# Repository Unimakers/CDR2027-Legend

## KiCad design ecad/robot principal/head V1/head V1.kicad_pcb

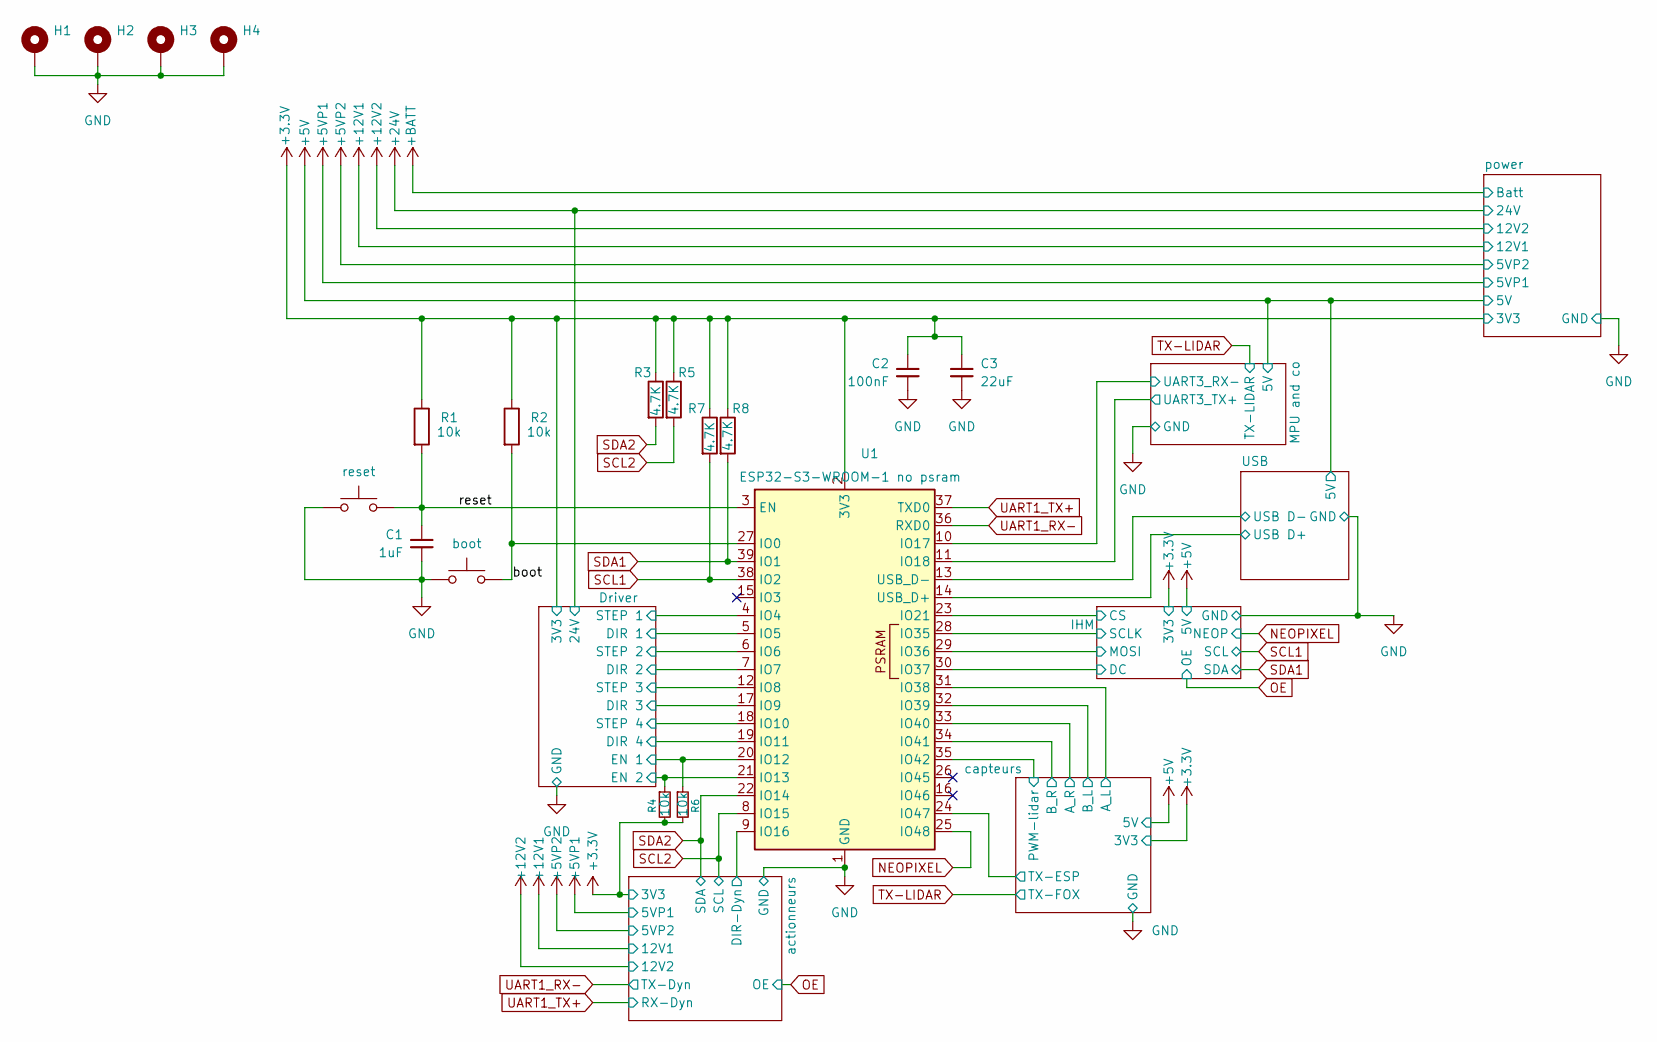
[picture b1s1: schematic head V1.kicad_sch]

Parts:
C1: 1uF; C_0805_2012Metric_Pad1.18x1.45mm_HandSolder
C2: 100nF; C_0805_2012Metric_Pad1.18x1.45mm_HandSolder
C3: 22uF; C_0805_2012Metric_Pad1.18x1.45mm_HandSolder
H1, H2, H3, H4: MountingHole_Pad; MountingHole_3.2mm_M3_Pad_Via
R1, R2, R4, R6: 10k; R_0805_2012Metric_Pad1.20x1.40mm_HandSolder
R3, R5, R7, R8: 4.7K; R_0805_2012Metric_Pad1.20x1.40mm_HandSolder
SW1: reset; SW_Push_SPST_NO_Alps_SKRK
SW2: boot; SW_Push_SPST_NO_Alps_SKRK
U1: ESP32-S3-WROOM-1 no psram; ESP32-S3-WROOM-1

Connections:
+3.3V: C2.1, C3.1, R1.1, R2.1, R3.1, R4.2, R5.1, R6.2, R7.1, R8.1, U1.2 (3V3); also elsewhere on the board
/Driver/DIR 1: U1.5 (IO5); also elsewhere on the board
/Driver/DIR 2: U1.7 (IO7); also elsewhere on the board
/Driver/DIR 3: U1.17 (IO9); also elsewhere on the board
/Driver/DIR 4: U1.19 (IO11); also elsewhere on the board
/Driver/EN 1: R6.1, U1.20 (IO12); also elsewhere on the board
/Driver/EN 2: R4.1, U1.21 (IO13); also elsewhere on the board
/Driver/STEP 1: U1.4 (IO4); also elsewhere on the board
/Driver/STEP 2: U1.6 (IO6); also elsewhere on the board
/Driver/STEP 3: U1.12 (IO8); also elsewhere on the board
/Driver/STEP 4: U1.18 (IO10); also elsewhere on the board
/IHM/CS: U1.23 (IO21); also elsewhere on the board
/IHM/DC: U1.30 (IO37); also elsewhere on the board
/IHM/MOSI: U1.29 (IO36); also elsewhere on the board
/IHM/SCLK: U1.28 (IO35); also elsewhere on the board
/MPU and co/UART3_RX-: U1.10 (IO17); also elsewhere on the board
/MPU and co/UART3_TX+: U1.11 (IO18); also elsewhere on the board
/USB/USB D+: U1.14 (USB_D+); also elsewhere on the board
/USB/USB D-: U1.13 (USB_D-); also elsewhere on the board
/actionneurs/DIR-Dyn: U1.9 (IO16); also elsewhere on the board
/boot: R2.2, SW2.2, U1.27 (IO0)
/capteurs/A_L: U1.31 (IO38); also elsewhere on the board
/capteurs/A_R: U1.33 (IO40); also elsewhere on the board
/capteurs/B_L: U1.32 (IO39); also elsewhere on the board
/capteurs/B_R: U1.34 (IO41); also elsewhere on the board
/capteurs/PWM-lidar: U1.35 (IO42); also elsewhere on the board
/capteurs/TX-ESP: U1.24 (IO47); also elsewhere on the board
/reset: C1.1, R1.2, SW1.2, U1.3 (EN)
GND: C1.2, C2.2, C3.2, H1.1 (1_1), H2.1 (1_1), H3.1 (1_1), H4.1 (1_1), SW1.1, SW2.1, U1.1 (GND), U1.40 (GND), U1.41 (GND); also elsewhere on the board
NEOPIXEL: U1.25 (IO48); also elsewhere on the board
SCL1: R7.2, U1.38 (IO2); also elsewhere on the board
SCL2: R5.2, U1.8 (IO15); also elsewhere on the board
SDA1: R8.2, U1.39 (IO1); also elsewhere on the board
SDA2: R3.2, U1.22 (IO14); also elsewhere on the board
UART1_RX-: U1.36 (RXD0); also elsewhere on the board
UART1_TX+: U1.37 (TXD0); also elsewhere on the board

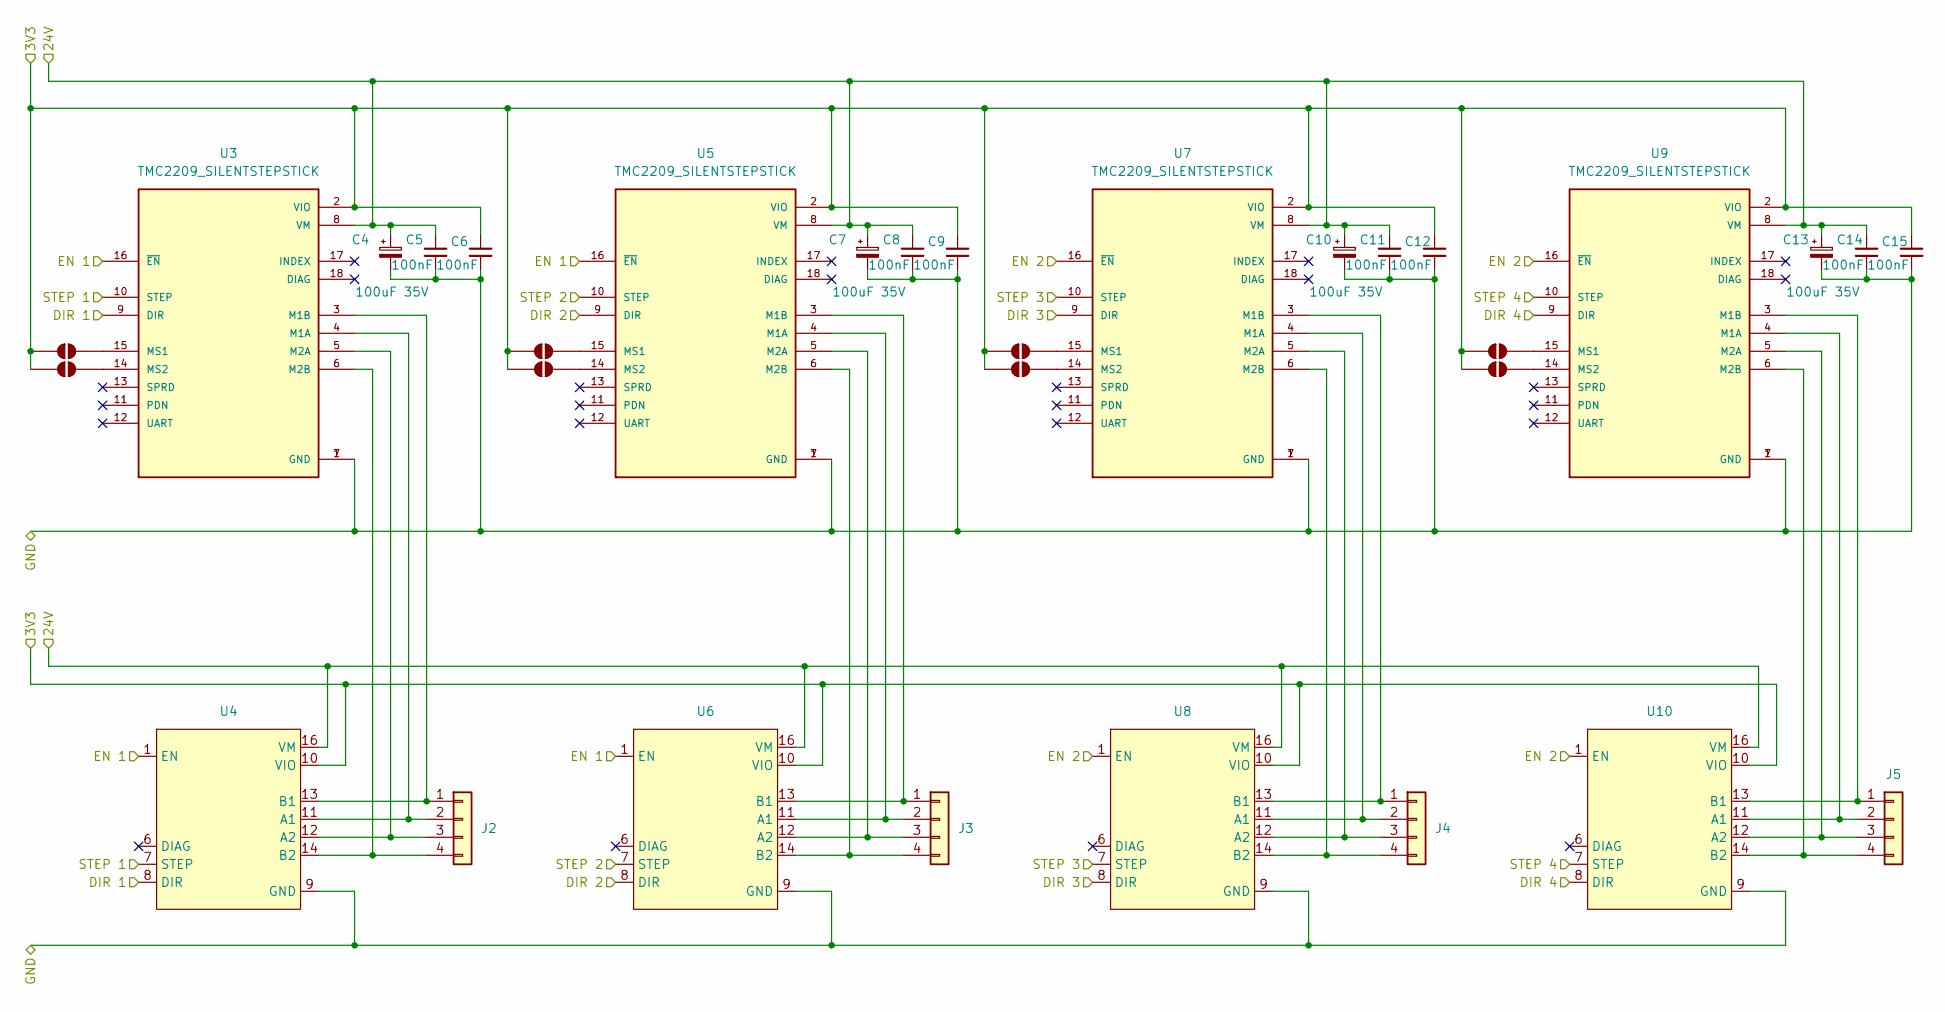
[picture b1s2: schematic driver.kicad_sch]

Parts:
C4, C7, C10, C13: 100uF 35V; CP_Radial_D6.3mm_P2.50mm
C5, C6, C8, C9, C11, C12, C14, C15: 100nF; C_0805_2012Metric_Pad1.18x1.45mm_HandSolder
J2, J3, J4, J5: Conn_01x04; Molex_KK-254_AE-6410-04A_1x04_P2.54mm_Vertical
JP1, JP2, JP3, JP4, JP5, JP6, JP7, JP8: SolderJumper_2_Open; SolderJumper-2_P1.3mm_Open_RoundedPad1.0x1.5mm
U3, U5, U7, U9: TMC2209_SILENTSTEPSTICK; MODULE_TMC2209_SILENTSTEPSTICK; PARTREV 1.20
U4, U6, U8, U10: ez 2209

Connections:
+3.3V: C6.1, C9.1, C12.1, C15.1, JP1.1 (A), JP2.1 (A), JP3.1 (A), JP4.1 (A), JP5.1 (A), JP6.1 (A), JP7.1 (A), JP8.1 (A), U3.2 (VIO), U4.10 (VIO), U5.2 (VIO), U6.10 (VIO), U7.2 (VIO), U8.10 (VIO), U9.2 (VIO), U10.10 (VIO); also elsewhere on the board
+24V: C4.1, C5.1, C7.1, C8.1, C10.1, C11.1, C13.1, C14.1, U3.8 (VM), U4.16 (VM), U5.8 (VM), U6.16 (VM), U7.8 (VM), U8.16 (VM), U9.8 (VM), U10.16 (VM); also elsewhere on the board
/Driver/DIR 1: U3.9 (DIR), U4.8 (DIR); also elsewhere on the board
/Driver/DIR 2: U5.9 (DIR), U6.8 (DIR); also elsewhere on the board
/Driver/DIR 3: U7.9 (DIR), U8.8 (DIR); also elsewhere on the board
/Driver/DIR 4: U9.9 (DIR), U10.8 (DIR); also elsewhere on the board
/Driver/EN 1: U3.16 (~EN), U4.1 (EN), U5.16 (~EN), U6.1 (EN); also elsewhere on the board
/Driver/EN 2: U7.16 (~EN), U8.1 (EN), U9.16 (~EN), U10.1 (EN); also elsewhere on the board
/Driver/STEP 1: U3.10 (STEP), U4.7 (STEP); also elsewhere on the board
/Driver/STEP 2: U5.10 (STEP), U6.7 (STEP); also elsewhere on the board
/Driver/STEP 3: U7.10 (STEP), U8.7 (STEP); also elsewhere on the board
/Driver/STEP 4: U9.10 (STEP), U10.7 (STEP); also elsewhere on the board
GND: C4.2, C5.2, C6.2, C7.2, C8.2, C9.2, C10.2, C11.2, C12.2, C13.2, C14.2, C15.2, U3.1 (GND), U3.7 (GND), U4.9 (GND), U4.15 (GND), U5.1 (GND), U5.7 (GND), U6.9 (GND), U6.15 (GND), U7.1 (GND), U7.7 (GND), U8.9 (GND), U8.15 (GND), U9.1 (GND), U9.7 (GND), U10.9 (GND), U10.15 (GND); also elsewhere on the board
unnamed: J2.1, U3.3 (M1B), U4.13 (B1)
unnamed: J2.2, U3.4 (M1A), U4.11 (A1)
unnamed: J2.3, U3.5 (M2A), U4.12 (A2)
unnamed: J2.4, U3.6 (M2B), U4.14 (B2)
unnamed: J3.1, U5.3 (M1B), U6.13 (B1)
unnamed: J3.2, U5.4 (M1A), U6.11 (A1)
unnamed: J3.3, U5.5 (M2A), U6.12 (A2)
unnamed: J3.4, U5.6 (M2B), U6.14 (B2)
unnamed: J4.1, U7.3 (M1B), U8.13 (B1)
unnamed: J4.2, U7.4 (M1A), U8.11 (A1)
unnamed: J4.3, U7.5 (M2A), U8.12 (A2)
unnamed: J4.4, U7.6 (M2B), U8.14 (B2)
unnamed: J5.1, U9.3 (M1B), U10.13 (B1)
unnamed: J5.2, U9.4 (M1A), U10.11 (A1)
unnamed: J5.3, U9.5 (M2A), U10.12 (A2)
unnamed: J5.4, U9.6 (M2B), U10.14 (B2)
unnamed: JP1.2 (B), U3.15 (MS1)
unnamed: JP2.2 (B), U3.14 (MS2)
unnamed: JP3.2 (B), U5.15 (MS1)
unnamed: JP4.2 (B), U5.14 (MS2)
unnamed: JP5.2 (B), U7.15 (MS1)
unnamed: JP6.2 (B), U7.14 (MS2)
unnamed: JP7.2 (B), U9.15 (MS1)
unnamed: JP8.2 (B), U9.14 (MS2)

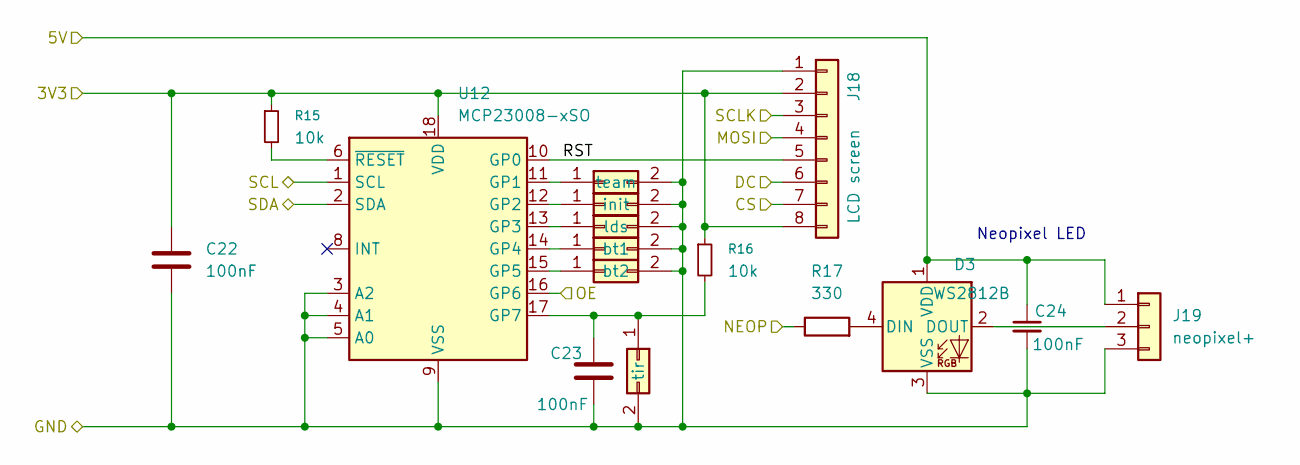
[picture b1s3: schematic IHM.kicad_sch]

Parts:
C22, C23, C24: 100nF; C_0805_2012Metric_Pad1.18x1.45mm_HandSolder
D3: WS2812B; LED_WS2812B_PLCC4_5.0x5.0mm_P3.2mm
J12: team; Molex_KK-254_AE-6410-02A_1x02_P2.54mm_Vertical
J13: init; Molex_KK-254_AE-6410-02A_1x02_P2.54mm_Vertical
J14: lds; Molex_KK-254_AE-6410-02A_1x02_P2.54mm_Vertical
J15: bt1; Molex_KK-254_AE-6410-02A_1x02_P2.54mm_Vertical
J16: bt2; Molex_KK-254_AE-6410-02A_1x02_P2.54mm_Vertical
J17: tir; Molex_KK-254_AE-6410-02A_1x02_P2.54mm_Vertical
J18: LCD screen; PinSocket_1x08_P2.54mm_Vertical
J19: neopixel+; Molex_KK-254_AE-6410-03A_1x03_P2.54mm_Vertical
R15, R16: 10k; R_0805_2012Metric_Pad1.20x1.40mm_HandSolder
R17: 330; R_0805_2012Metric_Pad1.20x1.40mm_HandSolder
U12: MCP23008-xSO; SOIC-18W_7.5x11.6mm_P1.27mm

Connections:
+3.3V: C22.1, J18.2, J18.8, R15.1, R16.1, U12.18 (VDD); also elsewhere on the board
+5V: C24.1, D3.1 (VDD), J19.1; also elsewhere on the board
/IHM/CS: J18.7; also elsewhere on the board
/IHM/DC: J18.6; also elsewhere on the board
/IHM/MOSI: J18.4; also elsewhere on the board
/IHM/RST: J18.5, U12.10 (GP0)
/IHM/SCLK: J18.3; also elsewhere on the board
GND: C22.2, C23.2, C24.2, D3.3 (VSS), J12.2, J13.2, J14.2, J15.2, J16.2, J17.2, J18.1, J19.3, U12.3 (A2), U12.4 (A1), U12.5 (A0), U12.9 (VSS); also elsewhere on the board
NEOPIXEL: R17.1; also elsewhere on the board
unnamed: D3.4 (DIN), R17.2
unnamed: D3.2 (DOUT), J19.2
unnamed: J12.1, U12.11 (GP1)
unnamed: J13.1, U12.12 (GP2)
unnamed: J14.1, U12.13 (GP3)
unnamed: J15.1, U12.14 (GP4)
unnamed: J16.1, U12.15 (GP5)
unnamed: C23.1, J17.1, R16.2, U12.17 (GP7)
unnamed: R15.2, U12.6 (~RESET)
OE: U12.16 (GP6); also elsewhere on the board
SCL1: U12.1 (SCL); also elsewhere on the board
SDA1: U12.2 (SDA); also elsewhere on the board

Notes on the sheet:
Neopixel LED

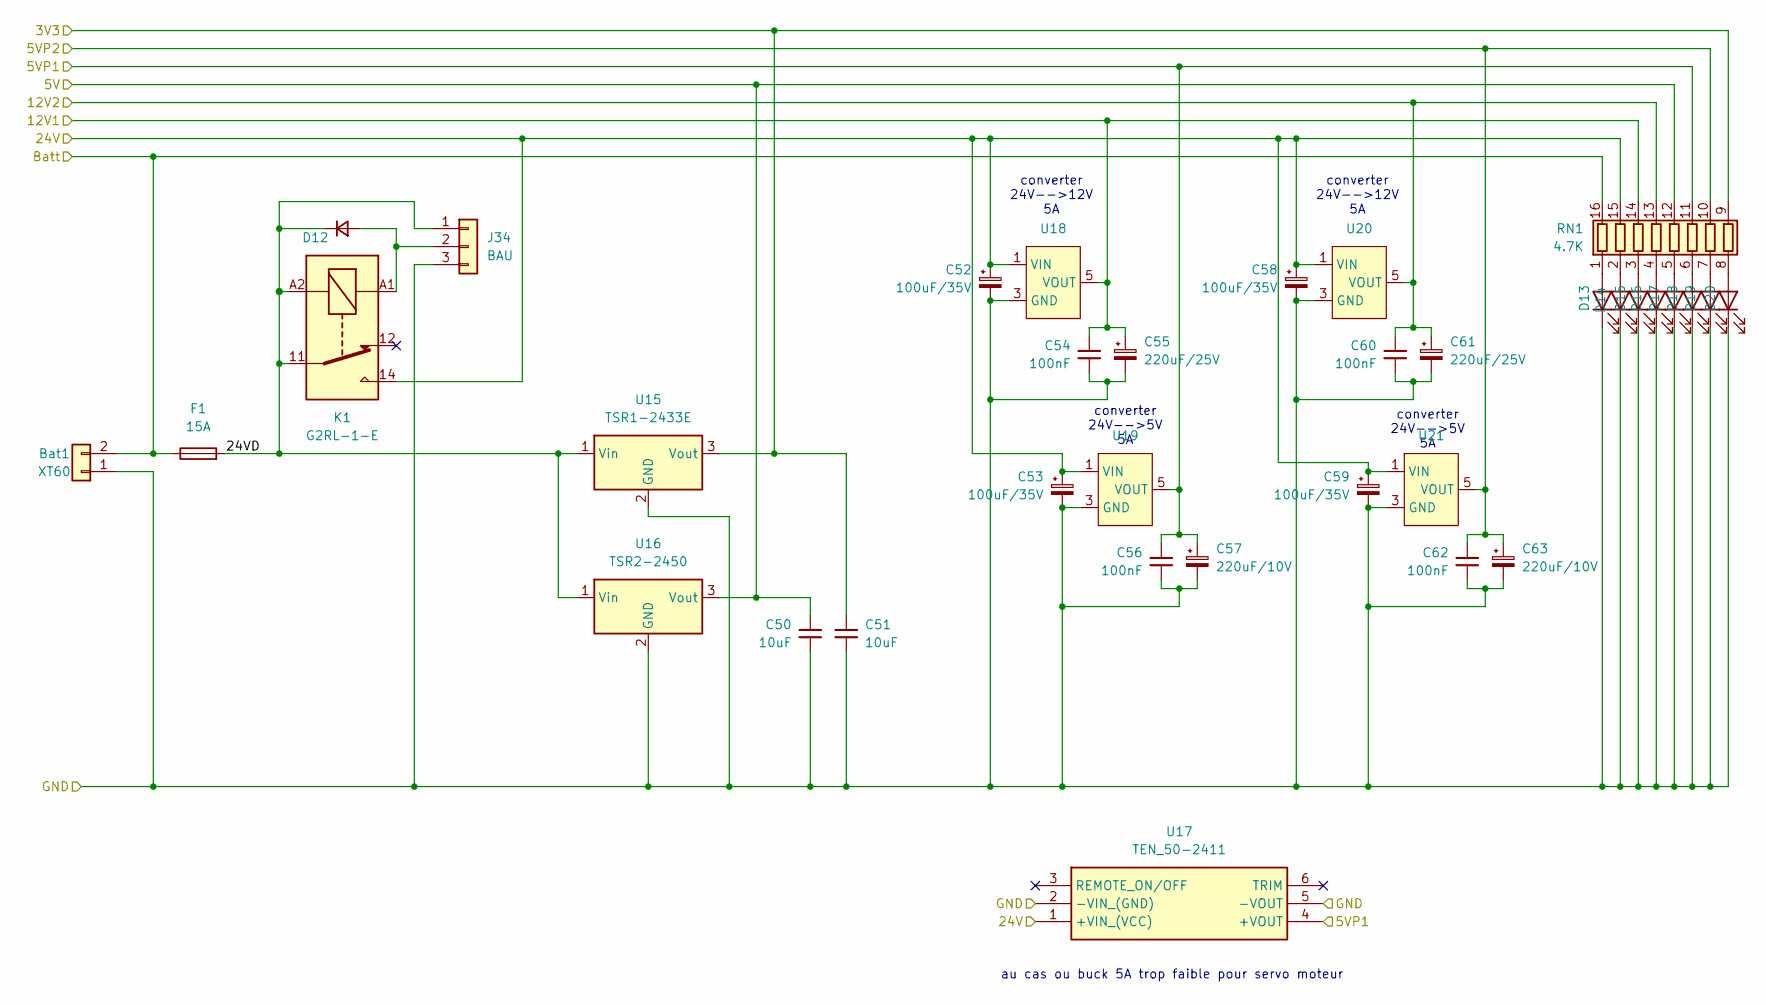
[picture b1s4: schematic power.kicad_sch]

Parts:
Bat1: XT60; AMASS_XT60-M_1x02_P7.20mm_Vertical
C50, C51: 10uF; C_0805_2012Metric_Pad1.18x1.45mm_HandSolder
C52, C53, C58, C59: 100uF/35V; CP_Radial_D6.3mm_P2.50mm
C54, C56, C60, C62: 100nF; C_0805_2012Metric_Pad1.18x1.45mm_HandSolder
C55, C61: 220uF/25V; CP_Radial_D8.0mm_P3.50mm
C57, C63: 220uF/10V; CP_Radial_D6.3mm_P2.50mm
D12: D_Small; D_SMA_Handsoldering
D13, D14, D15, D16, D17, D18, D19, D20: LED; LED_0805_2012Metric_Pad1.15x1.40mm_HandSolder
F1: 15A; Fuseholder_Blade_Mini_Keystone_3568
J34: BAU; Molex_KK-254_AE-6410-03A_1x03_P2.54mm_Vertical
K1: G2RL-1-E; Relay_SPDT_Omron_G2RL-1-E
RN1: 4.7K; R_Array_Convex_8x0602
U15: TSR1-2433E; Converter_DCDC_TRACO_TSR1-xxxxE_THT
U16: TSR2-2450; Converter_DCDC_TRACO_TSR2-xxxx_THT
U17: TEN_50-2411; Mouser Part Number 495-TEN-50-2411
U18, U19, U20, U21: Module_Buck_LMR51450_1x06_P2.54mm

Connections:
+3.3V: C51.1, RN1.9 (R8.2), U15.3 (Vout); also elsewhere on the board
+5V: C50.1, RN1.12 (R5.2), U16.3 (Vout); also elsewhere on the board
+5VP1: C56.1, C57.1, RN1.11 (R6.2), U17.4 (+VOUT), U19.5 (VOUT), U19.6 (VOUT); also elsewhere on the board
+5VP2: C62.1, C63.1, RN1.10 (R7.2), U21.5 (VOUT), U21.6 (VOUT); also elsewhere on the board
+12V1: C54.1, C55.1, RN1.14 (R3.2), U18.5 (VOUT), U18.6 (VOUT); also elsewhere on the board
+12V2: C60.1, C61.1, RN1.13 (R4.2), U20.5 (VOUT), U20.6 (VOUT); also elsewhere on the board
+24V: C52.1, C53.1, C58.1, C59.1, K1.14, RN1.15 (R2.2), U17.1 (+VIN_(VCC)), U18.1 (VIN), U18.2 (VIN), U19.1 (VIN), U19.2 (VIN), U20.1 (VIN), U20.2 (VIN), U21.1 (VIN), U21.2 (VIN); also elsewhere on the board
+BATT: Bat1.2, F1.1, RN1.16 (R1.2)
/power/24VD: D12.1 (K), F1.2, J34.1, K1.11, K1.A2, U15.1 (Vin), U16.1 (Vin)
GND: Bat1.1, C50.2, C51.2, C52.2, C53.2, C54.2, C55.2, C56.2, C57.2, C58.2, C59.2, C60.2, C61.2, C62.2, C63.2, D13.1 (K), D14.1 (K), D15.1 (K), D16.1 (K), D17.1 (K), D18.1 (K), D19.1 (K), D20.1 (K), J34.3, U15.2 (GND), U16.2 (GND), U17.2 (-VIN_(GND)), U17.5 (-VOUT), U18.3 (GND), U18.4 (GND), U19.3 (GND), U19.4 (GND), U20.3 (GND), U20.4 (GND), U21.3 (GND), U21.4 (GND); also elsewhere on the board
unnamed: D12.2 (A), J34.2, K1.A1
unnamed: D13.2 (A), RN1.1 (R1.1)
unnamed: D14.2 (A), RN1.2 (R2.1)
unnamed: D15.2 (A), RN1.3 (R3.1)
unnamed: D16.2 (A), RN1.4 (R4.1)
unnamed: D17.2 (A), RN1.5 (R5.1)
unnamed: D18.2 (A), RN1.6 (R6.1)
unnamed: D19.2 (A), RN1.7 (R7.1)
unnamed: D20.2 (A), RN1.8 (R8.1)

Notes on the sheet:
converter 24V-->12V 5A
converter 24V-->5V 5A
au cas ou buck 5A trop faible pour servo moteur

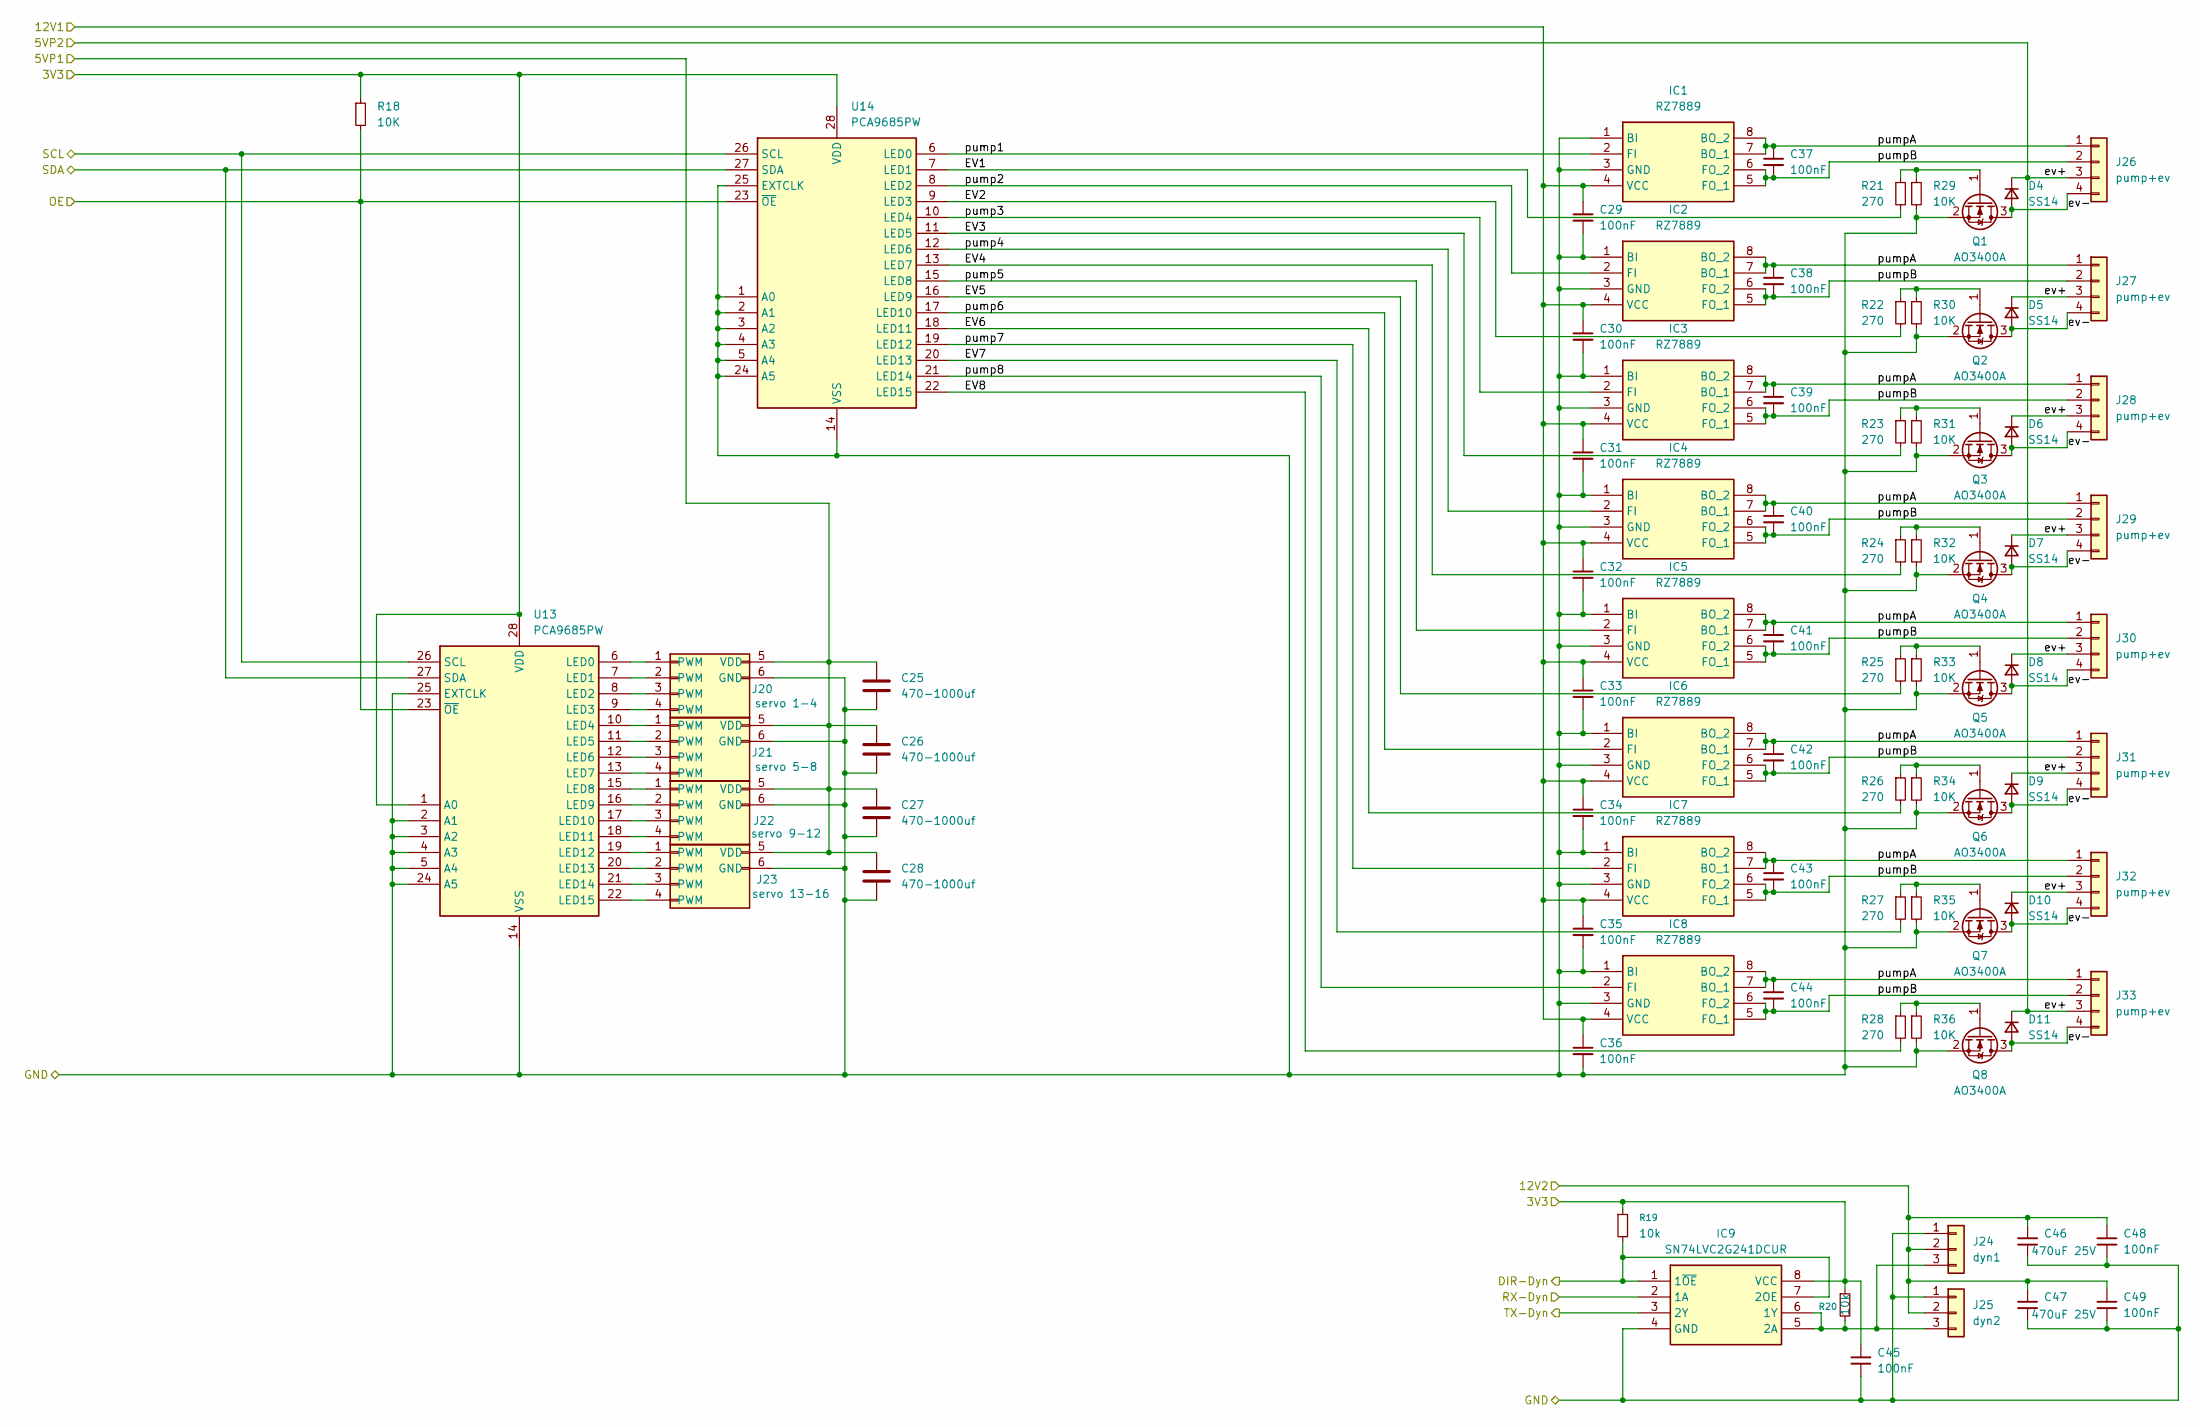
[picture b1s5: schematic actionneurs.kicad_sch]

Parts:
C25, C26, C27, C28: 470-1000uf; CP_Radial_D10.0mm_P5.00mm
C29, C30, C31, C32, C33, C34, C35, C36, C37, C38, C39, C40, C41, C42, C43, C44, C45, C48, C49: 100nF; C_0805_2012Metric_Pad1.18x1.45mm_HandSolder
C46, C47: 470uF 25V; CP_Radial_D10.0mm_P5.00mm
D4, D5, D6, D7, D8, D9, D10, D11: SS14; D_SMA
IC1, IC2, IC3, IC4, IC5, IC6, IC7, IC8: RZ7889; SOIC127P600X175-8N; Manufacturer_Part_Number RZ7889
IC9: SN74LVC2G241DCUR; SOP50P310X90-8N; Mouser Part Number 595-SN74LVC2G241DCUR
J20: servo 1-4; servo
J21: servo 5-8; servo
J22: servo 9-12; servo
J23: servo 13-16; servo
J24: dyn1; Molex_SPOX_5267-03A_1x03_P2.50mm_Vertical
J25: dyn2; Molex_SPOX_5267-03A_1x03_P2.50mm_Vertical
J26, J27, J28, J29, J30, J31, J32, J33: pump+ev; Molex_KK-254_AE-6410-04A_1x04_P2.54mm_Vertical
Q1, Q2, Q3, Q4, Q5, Q6, Q7, Q8: AO3400A; SOT-23
R18, R29, R30, R31, R32, R33, R34, R35, R36: 10K; R_0805_2012Metric_Pad1.20x1.40mm_HandSolder
R19, R20: 10k; R_0805_2012Metric_Pad1.20x1.40mm_HandSolder
R21, R22, R23, R24, R25, R26, R27, R28: 270; R_0805_2012Metric_Pad1.20x1.40mm_HandSolder
U13, U14: PCA9685PW; TSSOP-28_4.4x9.7mm_P0.65mm

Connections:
+3.3V: C45.1, IC9.8 (VCC), R18.1, R19.1, R20.1, U13.1 (A0), U13.28 (VDD), U14.28 (VDD); also elsewhere on the board
+5VP1: C25.1, C26.1, C27.1, C28.1, J20.5 (VDD), J20.7 (VDD), J20.9 (VDD), J20.11 (VDD), J21.5 (VDD), J21.7 (VDD), J21.9 (VDD), J21.11 (VDD), J22.5 (VDD), J22.7 (VDD), J22.9 (VDD), J22.11 (VDD), J23.5 (VDD), J23.7 (VDD), J23.9 (VDD), J23.11 (VDD); also elsewhere on the board
+5VP2: D4.1 (K), D5.1 (K), D6.1 (K), D7.1 (K), D8.1 (K), D9.1 (K), D10.1 (K), D11.1 (K), J26.3, J27.3, J28.3, J29.3, J30.3, J31.3, J32.3, J33.3; also elsewhere on the board
+12V1: C29.1, C30.1, C31.1, C32.1, C33.1, C34.1, C35.1, C36.1, IC1.4 (VCC), IC2.4 (VCC), IC3.4 (VCC), IC4.4 (VCC), IC5.4 (VCC), IC6.4 (VCC), IC7.4 (VCC), IC8.4 (VCC); also elsewhere on the board
+12V2: C46.1, C47.1, C48.1, C49.1, J24.2, J25.2; also elsewhere on the board
/actionneurs/DIR-Dyn: IC9.1 (1~OE), IC9.7 (2OE), R19.2; also elsewhere on the board
/actionneurs/EV1: R21.2, U14.7 (LED1)
/actionneurs/EV2: R22.2, U14.9 (LED3)
/actionneurs/EV3: R23.2, U14.11 (LED5)
/actionneurs/EV4: R24.2, U14.13 (LED7)
/actionneurs/EV5: R25.2, U14.16 (LED9)
/actionneurs/EV6: R26.2, U14.18 (LED11)
/actionneurs/EV7: R27.2, U14.20 (LED13)
/actionneurs/EV8: R28.2, U14.22 (LED15)
/actionneurs/ev-: D4.2 (A), D5.2 (A), D6.2 (A), D7.2 (A), D8.2 (A), D9.2 (A), D10.2 (A), D11.2 (A), J26.4, J27.4, J28.4, J29.4, J30.4, J31.4, J32.4, J33.4, Q1.3 (D), Q2.3 (D), Q3.3 (D), Q4.3 (D), Q5.3 (D), Q6.3 (D), Q7.3 (D), Q8.3 (D)
/actionneurs/pump1: IC1.2 (FI), U14.6 (LED0)
/actionneurs/pump2: IC2.2 (FI), U14.8 (LED2)
/actionneurs/pump3: IC3.2 (FI), U14.10 (LED4)
/actionneurs/pump4: IC4.2 (FI), U14.12 (LED6)
/actionneurs/pump5: IC5.2 (FI), U14.15 (LED8)
/actionneurs/pump6: IC6.2 (FI), U14.17 (LED10)
/actionneurs/pump7: IC7.2 (FI), U14.19 (LED12)
/actionneurs/pump8: IC8.2 (FI), U14.21 (LED14)
/actionneurs/pumpA: C37.1, C38.1, C39.1, C40.1, C41.1, C42.1, C43.1, C44.1, IC1.7 (BO_1), IC1.8 (BO_2), IC2.7 (BO_1), IC2.8 (BO_2), IC3.7 (BO_1), IC3.8 (BO_2), IC4.7 (BO_1), IC4.8 (BO_2), IC5.7 (BO_1), IC5.8 (BO_2), IC6.7 (BO_1), IC6.8 (BO_2), IC7.7 (BO_1), IC7.8 (BO_2), IC8.7 (BO_1), IC8.8 (BO_2), J26.1, J27.1, J28.1, J29.1, J30.1, J31.1, J32.1, J33.1
/actionneurs/pumpB: C37.2, C38.2, C39.2, C40.2, C41.2, C42.2, C43.2, C44.2, IC1.5 (FO_1), IC1.6 (FO_2), IC2.5 (FO_1), IC2.6 (FO_2), IC3.5 (FO_1), IC3.6 (FO_2), IC4.5 (FO_1), IC4.6 (FO_2), IC5.5 (FO_1), IC5.6 (FO_2), IC6.5 (FO_1), IC6.6 (FO_2), IC7.5 (FO_1), IC7.6 (FO_2), IC8.5 (FO_1), IC8.6 (FO_2), J26.2, J27.2, J28.2, J29.2, J30.2, J31.2, J32.2, J33.2
GND: C25.2, C26.2, C27.2, C28.2, C29.2, C30.2, C31.2, C32.2, C33.2, C34.2, C35.2, C36.2, C45.2, C46.2, C47.2, C48.2, C49.2, IC1.1 (BI), IC1.3 (GND), IC2.1 (BI), IC2.3 (GND), IC3.1 (BI), IC3.3 (GND), IC4.1 (BI), IC4.3 (GND), IC5.1 (BI), IC5.3 (GND), IC6.1 (BI), IC6.3 (GND), IC7.1 (BI), IC7.3 (GND), IC8.1 (BI), IC8.3 (GND), IC9.4 (GND), J20.6 (GND), J20.8 (GND), J20.10 (GND), J20.12 (GND), J21.6 (GND), J21.8 (GND), J21.10 (GND), J21.12 (GND), J22.6 (GND), J22.8 (GND), J22.10 (GND), J22.12 (GND), J23.6 (GND), J23.8 (GND), J23.10 (GND), J23.12 (GND), J24.1, J25.1, Q1.2 (S), Q2.2 (S), Q3.2 (S), Q4.2 (S), Q5.2 (S), Q6.2 (S), Q7.2 (S), Q8.2 (S), R29.2, R30.2, R31.2, R32.2, R33.2, R34.2, R35.2, R36.2, U13.2 (A1), U13.3 (A2), U13.4 (A3), U13.5 (A4), U13.14 (VSS), U13.24 (A5), U13.25 (EXTCLK), U14.1 (A0), U14.2 (A1), U14.3 (A2), U14.4 (A3), U14.5 (A4), U14.14 (VSS), U14.24 (A5), U14.25 (EXTCLK); also elsewhere on the board
unnamed: IC9.5 (2A), IC9.6 (1Y), J24.3, J25.3, R20.2
unnamed: Q1.1 (G), R21.1, R29.1
unnamed: Q2.1 (G), R22.1, R30.1
unnamed: Q3.1 (G), R23.1, R31.1
unnamed: Q4.1 (G), R24.1, R32.1
unnamed: Q5.1 (G), R25.1, R33.1
unnamed: Q6.1 (G), R26.1, R34.1
unnamed: Q7.1 (G), R27.1, R35.1
unnamed: Q8.1 (G), R28.1, R36.1
unnamed: J20.1 (PWM), U13.6 (LED0)
unnamed: J20.2 (PWM), U13.7 (LED1)
unnamed: J20.3 (PWM), U13.8 (LED2)
unnamed: J20.4 (PWM), U13.9 (LED3)
unnamed: J21.1 (PWM), U13.10 (LED4)
unnamed: J21.2 (PWM), U13.11 (LED5)
unnamed: J21.3 (PWM), U13.12 (LED6)
unnamed: J21.4 (PWM), U13.13 (LED7)
unnamed: J22.1 (PWM), U13.15 (LED8)
unnamed: J22.2 (PWM), U13.16 (LED9)
unnamed: J22.3 (PWM), U13.17 (LED10)
unnamed: J22.4 (PWM), U13.18 (LED11)
unnamed: J23.1 (PWM), U13.19 (LED12)
unnamed: J23.2 (PWM), U13.20 (LED13)
unnamed: J23.3 (PWM), U13.21 (LED14)
unnamed: J23.4 (PWM), U13.22 (LED15)
OE: R18.2, U13.23 (~OE), U14.23 (~OE); also elsewhere on the board
SCL2: U13.26 (SCL), U14.26 (SCL); also elsewhere on the board
SDA2: U13.27 (SDA), U14.27 (SDA); also elsewhere on the board
UART1_RX-: IC9.3 (2Y); also elsewhere on the board
UART1_TX+: IC9.2 (1A); also elsewhere on the board

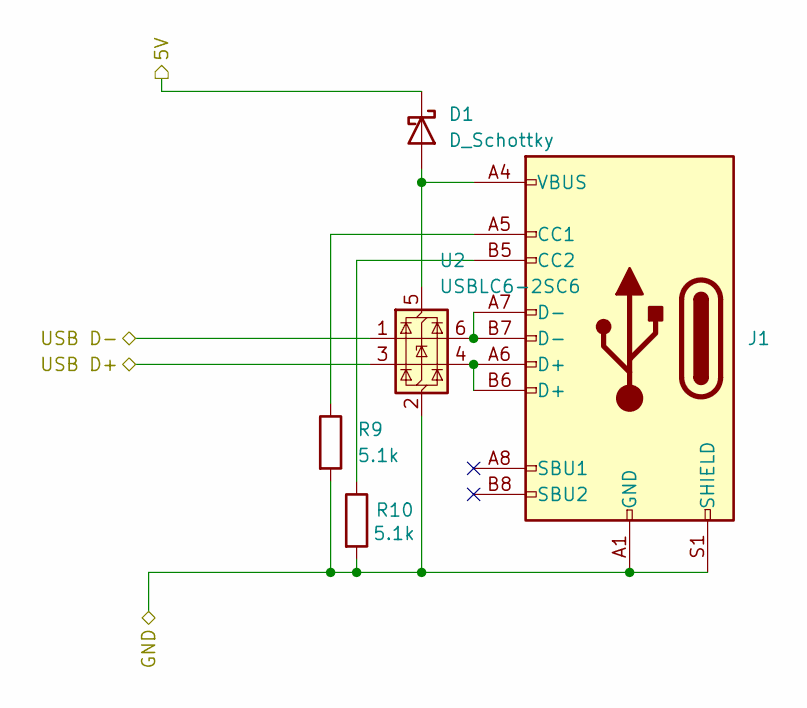
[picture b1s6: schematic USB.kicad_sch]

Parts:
D1: D_Schottky; D_0805_2012Metric_Pad1.15x1.40mm_HandSolder
J1: USB_C_Receptacle_USB2.0_16P; USB_C_Receptacle_HRO_TYPE-C-31-M-12
R9, R10: 5.1k; R_0805_2012Metric_Pad1.20x1.40mm_HandSolder
U2: USBLC6-2SC6; SOT-23-6

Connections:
+5V: D1.1 (K); also elsewhere on the board
/USB/USB D+: U2.3 (I/O2); also elsewhere on the board
/USB/USB D-: U2.1 (I/O1); also elsewhere on the board
GND: J1.A1 (GND), J1.A12 (GND), J1.B1 (GND), J1.B12 (GND), J1.S1 (SHIELD), R9.2, R10.2, U2.2 (GND); also elsewhere on the board
unnamed: D1.2 (A), J1.A4 (VBUS), J1.A9 (VBUS), J1.B4 (VBUS), J1.B9 (VBUS), U2.5 (VBUS)
unnamed: J1.A5 (CC1), R9.1
unnamed: J1.B5 (CC2), R10.1
unnamed: J1.A6 (D+), J1.B6 (D+), U2.4 (I/O2)
unnamed: J1.A7 (D-), J1.B7 (D-), U2.6 (I/O1)

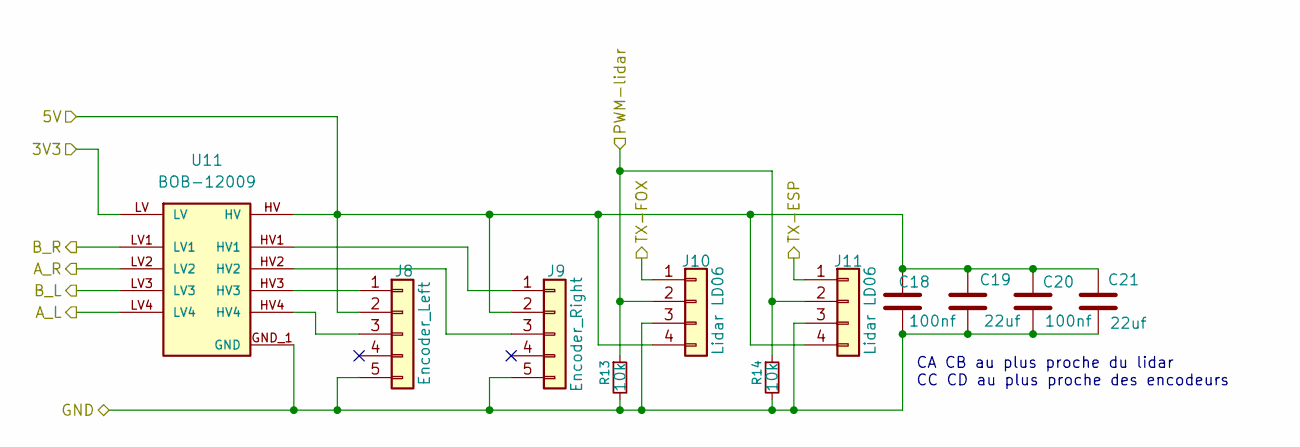
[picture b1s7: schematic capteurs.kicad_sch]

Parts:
C18, C20: 100nf; C_0805_2012Metric_Pad1.18x1.45mm_HandSolder
C19, C21: 22uf; C_0805_2012Metric_Pad1.18x1.45mm_HandSolder
J8: Encoder_Left; Molex_KK-254_AE-6410-05A_1x05_P2.54mm_Vertical
J9: Encoder_Right; Molex_KK-254_AE-6410-05A_1x05_P2.54mm_Vertical
J10, J11: Lidar LD06; Molex_KK-254_AE-6410-04A_1x04_P2.54mm_Vertical
R13, R14: 10k; R_0805_2012Metric_Pad1.20x1.40mm_HandSolder
U11: BOB-12009; CONV_BOB-12009; PARTREV 01

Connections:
+3.3V: U11.LV; also elsewhere on the board
+5V: C18.1, C19.1, C20.1, C21.1, J8.2, J9.2, J10.4, J11.4, U11.HV; also elsewhere on the board
/capteurs/A_L: U11.LV4; also elsewhere on the board
/capteurs/A_R: U11.LV2; also elsewhere on the board
/capteurs/B_L: U11.LV3; also elsewhere on the board
/capteurs/B_R: U11.LV1; also elsewhere on the board
/capteurs/PWM-lidar: J10.2, J11.2, R13.1, R14.1; also elsewhere on the board
/capteurs/TX-ESP: J11.1; also elsewhere on the board
GND: C18.2, C19.2, C20.2, C21.2, J8.5, J9.5, J10.3, J11.3, R13.2, R14.2, U11.GND_1 (GND), U11.GND_2 (GND); also elsewhere on the board
unnamed: J8.1, U11.HV3
unnamed: J8.3, U11.HV4
unnamed: J9.1, U11.HV1
unnamed: J9.3, U11.HV2
TX-LIDAR: J10.1; also elsewhere on the board

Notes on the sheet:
CA CB au plus proche du lidar CC CD au plus proche des encodeurs

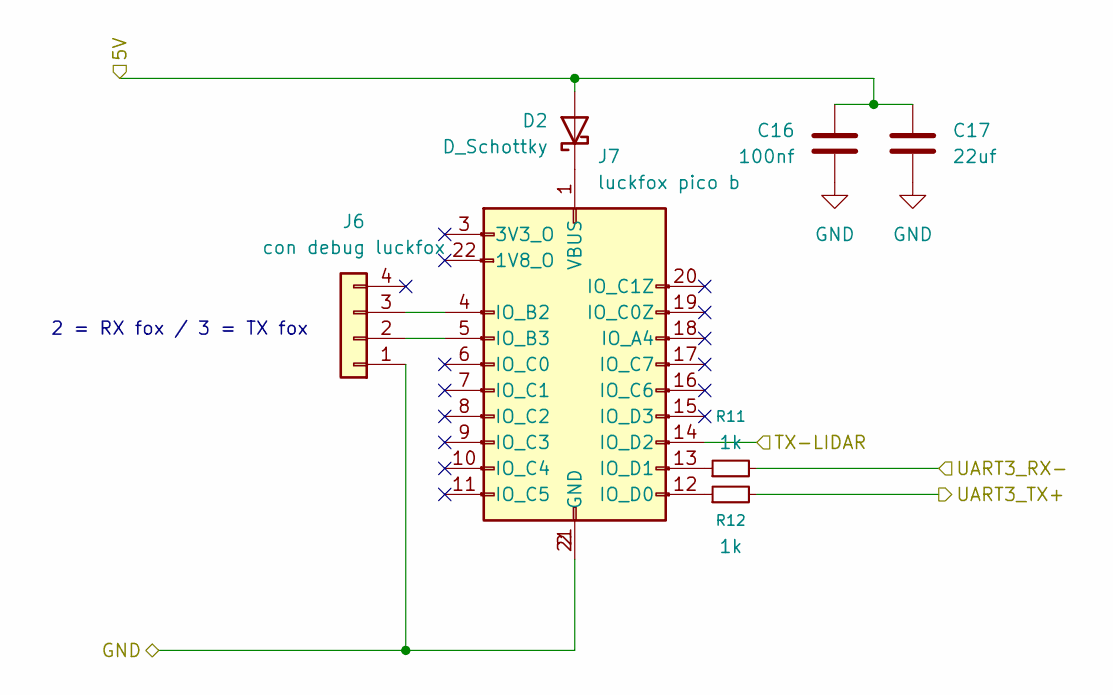
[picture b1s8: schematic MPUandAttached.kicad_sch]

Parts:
C16: 100nf; C_0805_2012Metric_Pad1.18x1.45mm_HandSolder
C17: 22uf; C_0805_2012Metric_Pad1.18x1.45mm_HandSolder
D2: D_Schottky; D_0805_2012Metric_Pad1.15x1.40mm_HandSolder
J6: con debug luckfox; Molex_KK-254_AE-6410-04A_1x04_P2.54mm_Vertical
J7: luckfox pico b; Luckfox_Pico_Mini_THT_2x11_P2.54mm_Row17.78mm
R11, R12: 1k; R_0805_2012Metric_Pad1.20x1.40mm_HandSolder

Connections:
+5V: C16.1, C17.1, D2.2 (A); also elsewhere on the board
/MPU and co/UART3_RX-: R11.2; also elsewhere on the board
/MPU and co/UART3_TX+: R12.2; also elsewhere on the board
GND: C16.2, C17.2, J6.1, J7.2 (GND), J7.21 (GND); also elsewhere on the board
unnamed: D2.1 (K), J7.1 (VBUS)
unnamed: J6.2, J7.5 (IO_B3)
unnamed: J6.3, J7.4 (IO_B2)
unnamed: J7.12 (IO_D0), R12.1
unnamed: J7.13 (IO_D1), R11.1
TX-LIDAR: J7.14 (IO_D2); also elsewhere on the board

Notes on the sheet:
2 = RX fox / 3 = TX fox
